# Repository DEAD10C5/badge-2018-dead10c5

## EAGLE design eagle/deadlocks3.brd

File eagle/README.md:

# Run DRC check
http://docs.oshpark.com/design-tools/eagle/design-rules-files/

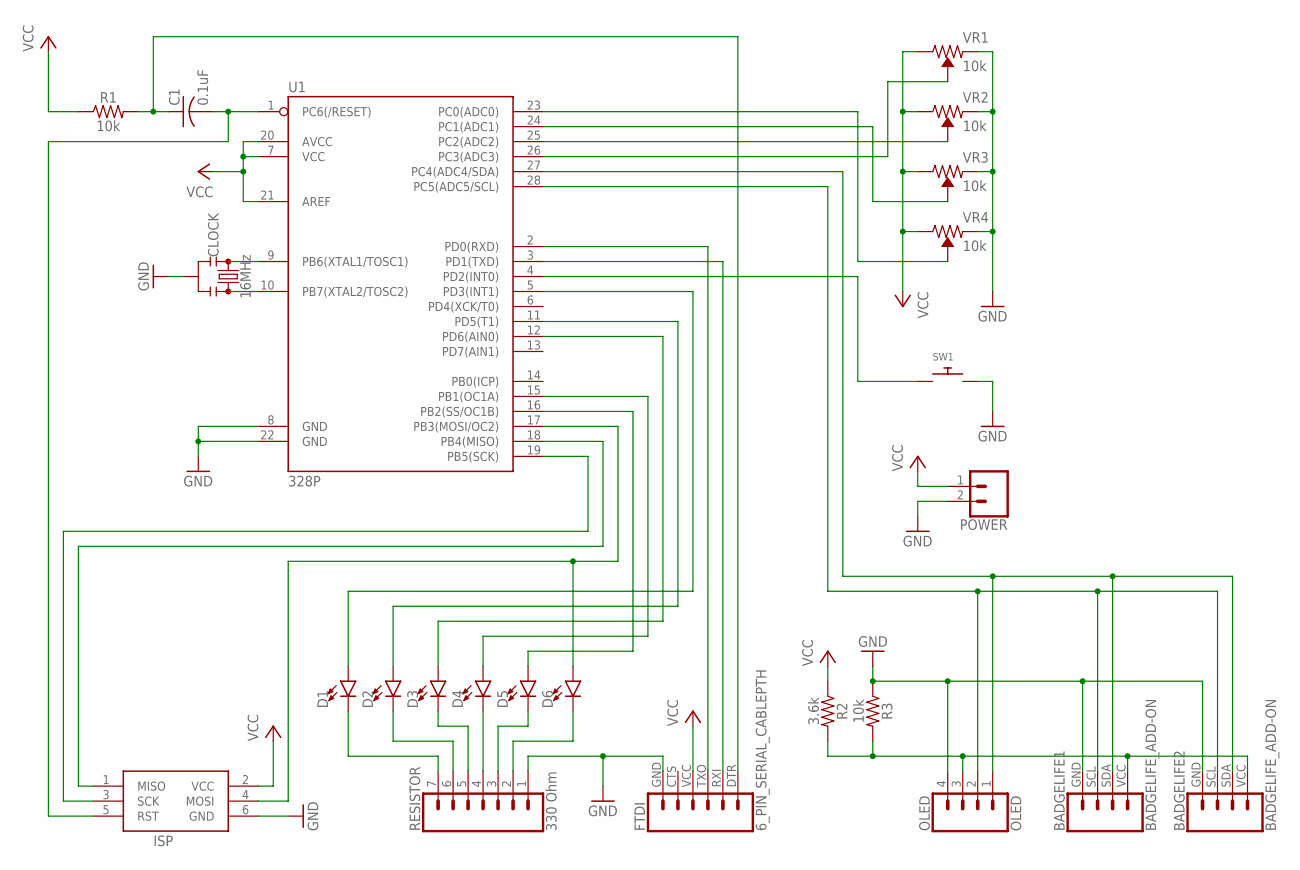
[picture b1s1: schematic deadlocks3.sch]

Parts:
BADGELIFE1, BADGELIFE2: BADGELIFE_ADD-ON
C1: 0.1uF; C025-024X044
CLOCK: 16MHz; RESONATOR-PTH-7.6X3.8
D1, D2, D3, D4, D5, D6: LED5MM; LED_5MM
FTDI: 6_PIN_SERIAL_CABLEPTH; FTDI_BASIC
ISP: AVRISP-6; AVRISP
OLED: OLED; 1X04
POWER: CONN_02; 1X02
R1, R3: 10k; AXIAL-0.3
R2: 3.6k; AXIAL-0.3
RESISTOR: 330 Ohm; 1X07
SW1: SWITCH_PUSHBUTTONEVQ-PE; TACT_PANA-EVQ
U1: 328P; DIP28
VR1, VR2, VR3, VR4: 10k; TRIMPOT-PTH-3386U

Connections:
GND: BADGELIFE1.GND (4), BADGELIFE2.GND (4), CLOCK.2, FTDI.GND (6), ISP.6 (GND), OLED.4, POWER.2, R3.P$1 (1), RESISTOR.1, SW1.P$2, U1.8 (GND), U1.22 (GND), VR1.1 (CCW), VR2.1 (CCW), VR3.1 (CCW), VR4.1 (CCW)
unnamed: U1.26 (PC3(ADC3)), VR1.2 (WIPER)
unnamed: CLOCK.1, U1.9 (PB6(XTAL1/TOSC1))
unnamed: CLOCK.3, U1.10 (PB7(XTAL2/TOSC2))
unnamed: U1.25 (PC2(ADC2)), VR2.2 (WIPER)
unnamed: U1.24 (PC1(ADC1)), VR3.2 (WIPER)
unnamed: U1.23 (PC0(ADC0)), VR4.2 (WIPER)
unnamed: FTDI.RXI (2), U1.3 (PD1(TXD))
unnamed: FTDI.TXO (3), U1.2 (PD0(RXD))
unnamed: ISP.1 (MISO), U1.18 (PB4(MISO))
unnamed: BADGELIFE1.VCC (1), BADGELIFE2.VCC (1), OLED.3, R2.P$2 (2), R3.P$2 (2)
unnamed: C1.2, ISP.5 (RST), U1.1 (PC6(/RESET))
unnamed: D6.K (C), RESISTOR.2
unnamed: D5.K (C), RESISTOR.3
unnamed: D4.K (C), RESISTOR.4
unnamed: D3.K (C), RESISTOR.5
unnamed: D2.K (C), RESISTOR.6
unnamed: D1.K (C), RESISTOR.7
unnamed: D6.A, ISP.4 (MOSI), U1.17 (PB3(MOSI/OC2))
unnamed: D1.A, U1.5 (PD3(INT1))
unnamed: D2.A, U1.11 (PD5(T1))
unnamed: D3.A, U1.12 (PD6(AIN0))
unnamed: D4.A, U1.15 (PB1(OC1A))
unnamed: D5.A, U1.16 (PB2(SS/OC1B))
unnamed: ISP.3 (SCK), U1.19 (PB5(SCK))
unnamed: SW1.P$1, U1.4 (PD2(INT0))
unnamed: BADGELIFE1.SDA (2), BADGELIFE2.SDA (2), OLED.1, U1.27 (PC4(ADC4/SDA))
unnamed: C1.1, FTDI.DTR (1), R1.P$2 (2)
unnamed: BADGELIFE1.SCL (3), BADGELIFE2.SCL (3), OLED.2, U1.28 (PC5(ADC5/SCL))
VCC: FTDI.VCC (4), ISP.2 (VCC), POWER.1, R1.P$1 (1), R2.P$1 (1), U1.7 (VCC), U1.20 (AVCC), U1.21 (AREF), VR1.3 (CW), VR2.3 (CW), VR3.3 (CW), VR4.3 (CW)

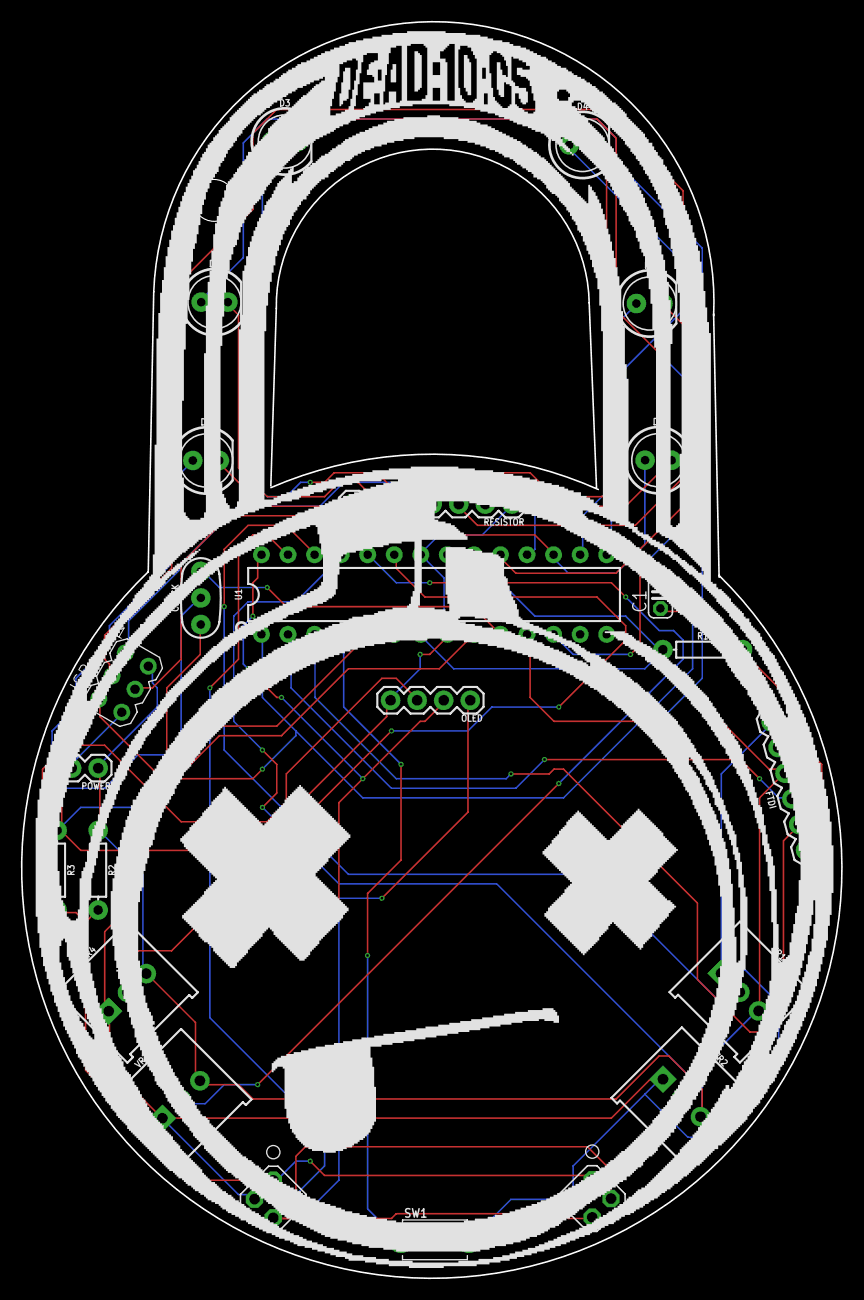
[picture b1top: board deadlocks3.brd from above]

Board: 2 copper layers, 78.4 x 120.2 mm, 24 parts (0 on the bottom side), 30 nets.

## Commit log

2018-04-07 new art
2018-04-07 Updates to BOM, board design, and datasheets.
2018-04-07 Updated board
2018-04-07 gerbers
2018-04-07 Finalized for prototype
2018-04-08 Cleaned up outdated designs and gerbers
2018-04-08 Re-arranged components, added a power input, and fixed the gerbers so Seeed can manufacture the prototypes.
2018-04-08 Forgot traces in the last version.
2018-04-08 A few more mods with new gerbers
2018-04-08 Updated BOM
2018-04-08 Added data sheet for battery holder
2018-04-09 dru file
2018-04-10 Added pic of Eagle rendering
2018-04-10 Added capture of Eagle rendering
2018-04-11 Updated BOM with resistors for voltage divider to produce 3.3v
2018-04-11 Updated arduino code to create random combinations. Also functionalized a few things.
2018-04-12 test art on eagle brd
2018-04-13 Updated arduino sketch to sweep LEDs more accurately.
2018-04-13 Added eagle screencap pic
2018-04-13 Added some more LED dancing routines
2018-04-16 Major updates to board and code
2018-04-17 Added artwork, add-on, i2c for oled
2018-04-17 Making sure repo is up-to-date
2018-04-17 More updates to the board and the code
2018-04-17 Cleaned up a few lingering files
2018-04-18 Major changes to code
2022-08-24 Add .whitesource configuration file
2023-12-15 Add renovate.json
2024-05-24 Add .whitesource configuration file (#1)

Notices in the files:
parts and their libraries:
SparkFun-Clocks: Licensing: Creative Commons ShareAlike 4.0 International - https://creativecommons.org/licenses/by-sa/4.0
